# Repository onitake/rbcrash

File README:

Rainbow Crash
=============

Colorful illumination - it's 20% cooler.

0. Contents
-----------

0. Contents
1. Description
2. License
3. Tools
4. Assembly
5. Compilation
6. Use
7. References

1. Description
--------------

Rainbow Crash is a high power color LED driver suitable for indoor lighting
applications. It is based on the TPS61165 constant current step-up regulator,
driving a chain of 350mA RGB LEDs. In the default configuration, the input
voltage should be around 12V for 8 LEDs in series. Lower voltages are possible,
as long as they are not below about 4V, or the microcontroller and the drivers
will be underpowered. Higher voltages should only be chosen if more than 8 LEDs
are driven.

2. License
----------

The circuit design is released under the [CERN Open Hardware License v1.2][ohl].
The firmware is covered by the [two-clause BSD license][bsd].

All documents are copyright (c) 2012-2014 by Gregor Riepl <onitake@gmail.com>.

The latest version can be retrieved from [Github][github].

3. Tools
--------

The original circuit was designed using [Eagle][eagle]. An updated version of
the circuit (2.0) was remade in [KiCAD][kicad].
The firmware for the microcontroller is based on a simple Makefile,
[avr-gcc][avrgcc], avr-libc and [avrdude][avrdude].
The code should be easily adaptable to other Atmel toolchains.

No [Arduino][arduino] or other external libraries were used; however, the code
includes register definitions for the [Arduino Uno][uno] development platform.
It was during the design phase and for debugging.

4. Assembly
-----------

Except for the constant current drivers and the corresponding inductors, most
parts should be easily obtainable from any electronic parts distributor.
Some of the capacitors are also less common (10uF and 4.7uF SMD0805 ceramic),
as well as the shunt resistors (0.57Ohms 1/8W).
SMD0805/2012 was chosen due to good hand solderability and power rating.

The inductor pads are generously dimensioned so they may accomodate various
kinds of SMD inductors. The layout is based on Wuerth Electronics WE-PD M-sized
shielded inductors, which are readily available from [Digi-Key][digikey].
Their continuous current rating should be above 700mA, preferably around 1A.

The intended IR receiver is a standard 38kHz demodulator with AGC. Other
parts with similar specifications may be used; they are mostly compatible
with each other and various consumer remotes.

It is recommended to employ a reflow process if producing multiple driver
boards. For single pieces or prototypes, hand soldering is also possible.

Production runs should not include the ISP pin header P6. Instead, order the
ATtiny25 microcontrollers preprogrammed or use a temporary connector to
transfer the firmware.

5. Compilation
--------------

All source code is contained in the single file pwm.c. Compiling is easiest
with the [avr-gcc][avrgcc] toolchain and GNU make. If you would like to use
other tools, make sure that your compiler understands ISO C99.

To flash the firmware, the Makefile includes a `flash` target that executes
[avrdude][avrdude] using options for the tinyUSB AVR ISP programmer.
avrdude supports many different programmers, see the manual for the appropriate
options.

6. Use
------

pwm.c includes preprogrammed IR codes for an old infrared remote found in the
garbage. It sends (incorrect) NEC codes, so those are the only IR codes
currently supported by the firmware. Sony and RC5 codes are still being worked
on, as well as a test tool for the Arduino Uno and possibly a firmware
extension to support live programming.

7. References
-------------

[ohl]: LICENSE-HARDWARE
[bsd]: LICENSE-SOFTWARE
[github]: https://github.com/onitake/rbcrash
[eagle]: http://www.cadsoft.de
[kicad]: http://www.kicad-pcb.org
[arduino]: http://arduino.cc
[uno]: http://arduino.cc/en/Main/ArduinoBoardUno
[digikey]: http://www.digikey.com/catalog/en/partgroup/we-pd-series/38220
[avrgcc]: http://www.nongnu.org/avr-libc/
[avrdude]: http://www.nongnu.org/avrdude/

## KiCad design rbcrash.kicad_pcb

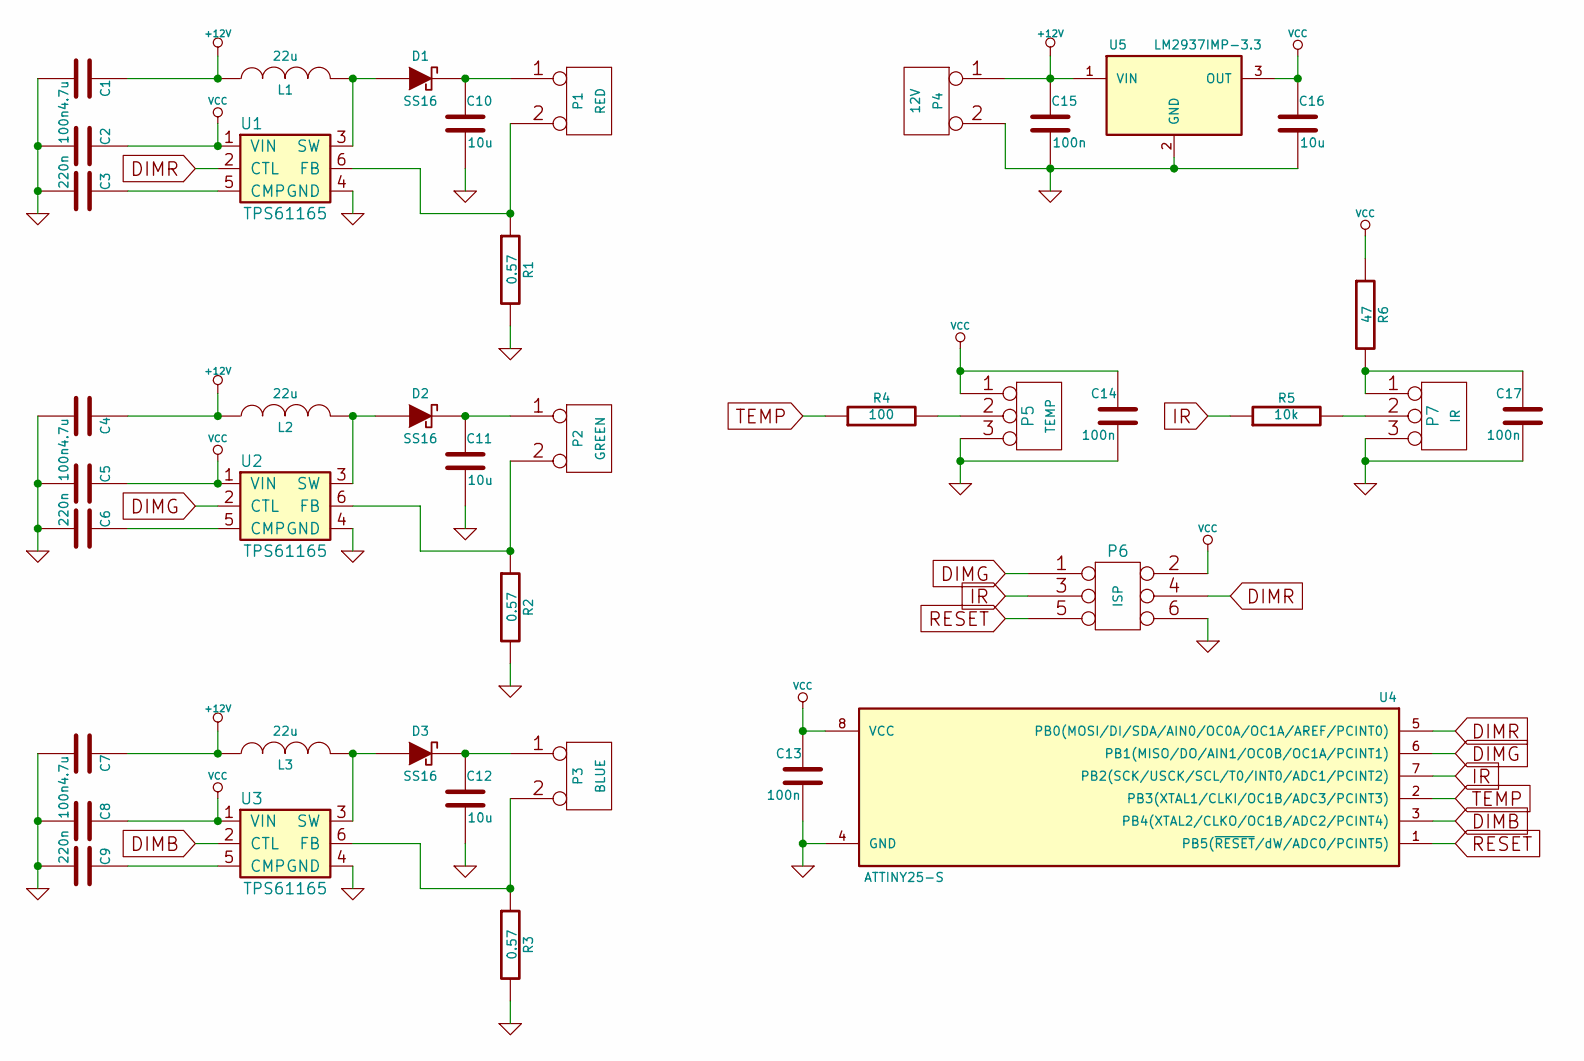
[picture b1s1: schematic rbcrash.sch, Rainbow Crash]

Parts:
C1, C4, C7: 4.7u; SM0805
C2, C5, C8, C13, C14, C15, C17: 100n; SM0805
C3, C6, C9: 220n; SM0805
C10, C11, C12, C16: 10u; SM0805
D1, D2, D3: SS16
L1, L2, L3: 22u
P1: RED
P2: GREEN
P3: BLUE
P4: 12V
P5: TEMP
P6: ISP
P7: IR
R1, R2, R3: 0.57; SM0805
R4: 100; SM0805
R5: 10k; SM0805
R6: 47; SM0805
U1, U2, U3: TPS61165
U4: ATTINY25-S; SO8-200
U5: LM2937IMP-3.3; SOT-223

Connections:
+12V: C1.1, C4.1, C7.1, C15.1, L1.1, L2.1, L3.1, P4.1, U5.1 (VIN)
DIMB: U3.2 (CTL), U4.3 (PB4(XTAL2/CLKO/OC1B/ADC2/PCINT4))
DIMG: P6.1, U2.2 (CTL), U4.6 (PB1(MISO/DO/AIN1/OC0B/OC1A/PCINT1))
DIMR: P6.4, U1.2 (CTL), U4.5 (PB0(MOSI/DI/SDA/AIN0/OC0A/OC1A/AREF/PCI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)
GND: C1.2, C2.2, C3.2, C4.2, C5.2, C6.2, C7.2, C8.2, C9.2, C10.2, C11.2, C12.2, C13.2, C14.2, C15.2, C16.2, C17.2, P4.2 (PM), P5.3, P6.6, P7.3, R1.2, R2.2, R3.2, U1.4 (GND), U2.4 (GND), U3.4 (GND), U4.4 (GND), U5.2 (GND)
IR: P6.3, R5.1, U4.7 (PB2(SCK/USCK/SCL/T0/INT0/ADC1/PCINT2))
unnamed: C12.1, D3.2 (K), P3.1
unnamed: C9.1, U3.5 (CMP)
unnamed: P3.2 (PM), R3.1, U3.6 (FB)
unnamed: D3.1 (A), L3.2, U3.3 (SW)
unnamed: P2.2 (PM), R2.1, U2.6 (FB)
unnamed: C6.1, U2.5 (CMP)
unnamed: C11.1, D2.2 (K), P2.1
unnamed: D2.1 (A), L2.2, U2.3 (SW)
unnamed: C17.1, P7.1, R6.2
unnamed: P7.2 (PM), R5.2
unnamed: P5.2 (PM), R4.2
unnamed: C3.1, U1.5 (CMP)
unnamed: C10.1, D1.2 (K), P1.1
unnamed: P1.2 (PM), R1.1, U1.6 (FB)
unnamed: D1.1 (A), L1.2, U1.3 (SW)
RESET: P6.5, U4.1 (PB5(~RESET~/dW/ADC0/PCINT5))
TEMP: R4.1, U4.2 (PB3(XTAL1/CLKI/OC1B/ADC3/PCINT3))
VCC: C2.1, C5.1, C8.1, C13.1, C14.1, C16.1, P5.1, P6.2, R6.1, U1.1 (VIN), U2.1 (VIN), U3.1 (VIN), U4.8 (VCC), U5.3 (OUT)

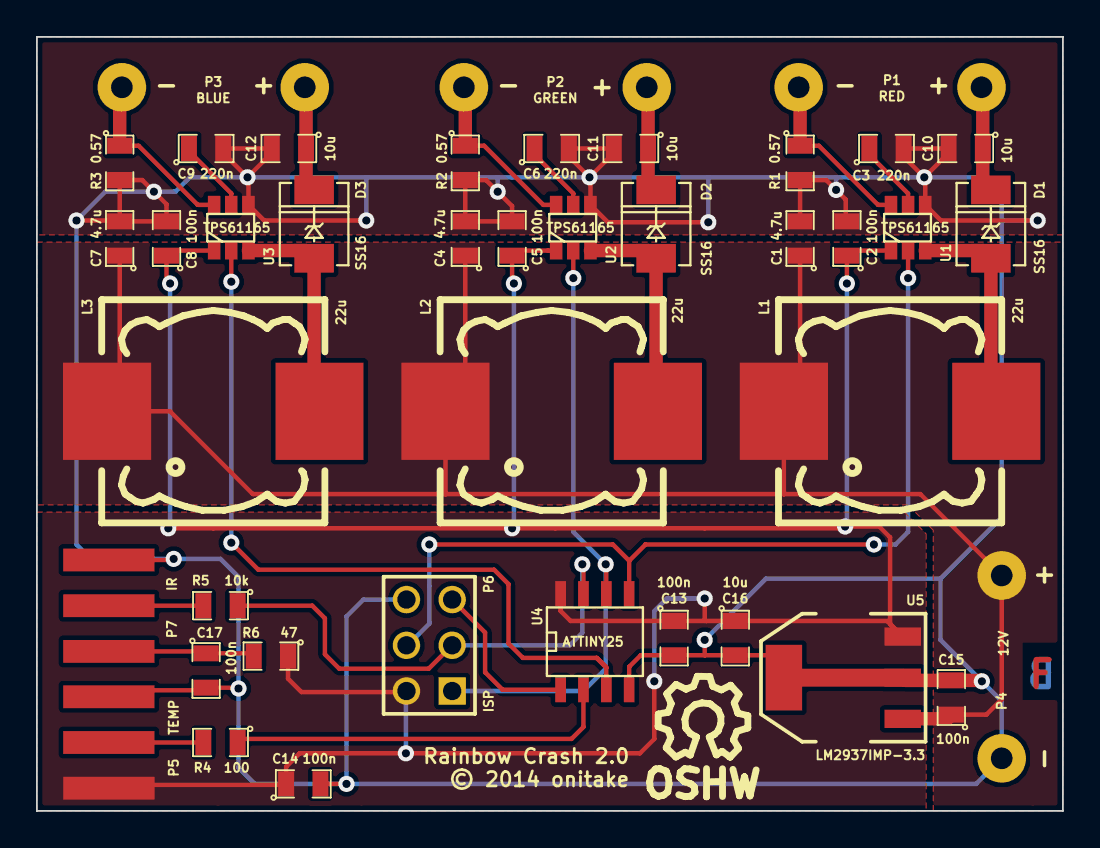
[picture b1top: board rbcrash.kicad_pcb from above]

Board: 2 copper layers, 57.0 x 43.0 mm, 42 parts (0 on the bottom side), 24 nets.

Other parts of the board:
SYM: Symbol_OSHW-Logo_SilkScreen_07Jul2012

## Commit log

2012-12-13 Created empty project with slightly non-descriptive README
2012-12-15 First checkin with circuit diagram, PCB, readme, license text and program code for rainbow color changer IR remote code is not working yet
2014-10-06 Redesign of circuit in KiCAD
2014-10-06 Improved clock generation script
    Conflicts:
    genclocks.pl
2014-10-06 Rewrote most of the code, using the ATtiny's PWM generators now.
2014-10-06 Updated Makefile for new code
2014-10-06 Added licenses and readme, updated firmware code header

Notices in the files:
rbcrash.kicad_pcb:
(c) 2012-2014 Gregor Riepl
© 2014 onitake
rbcrash.sch:
Copyright (c) 2012-2014 Gregor Riepl
